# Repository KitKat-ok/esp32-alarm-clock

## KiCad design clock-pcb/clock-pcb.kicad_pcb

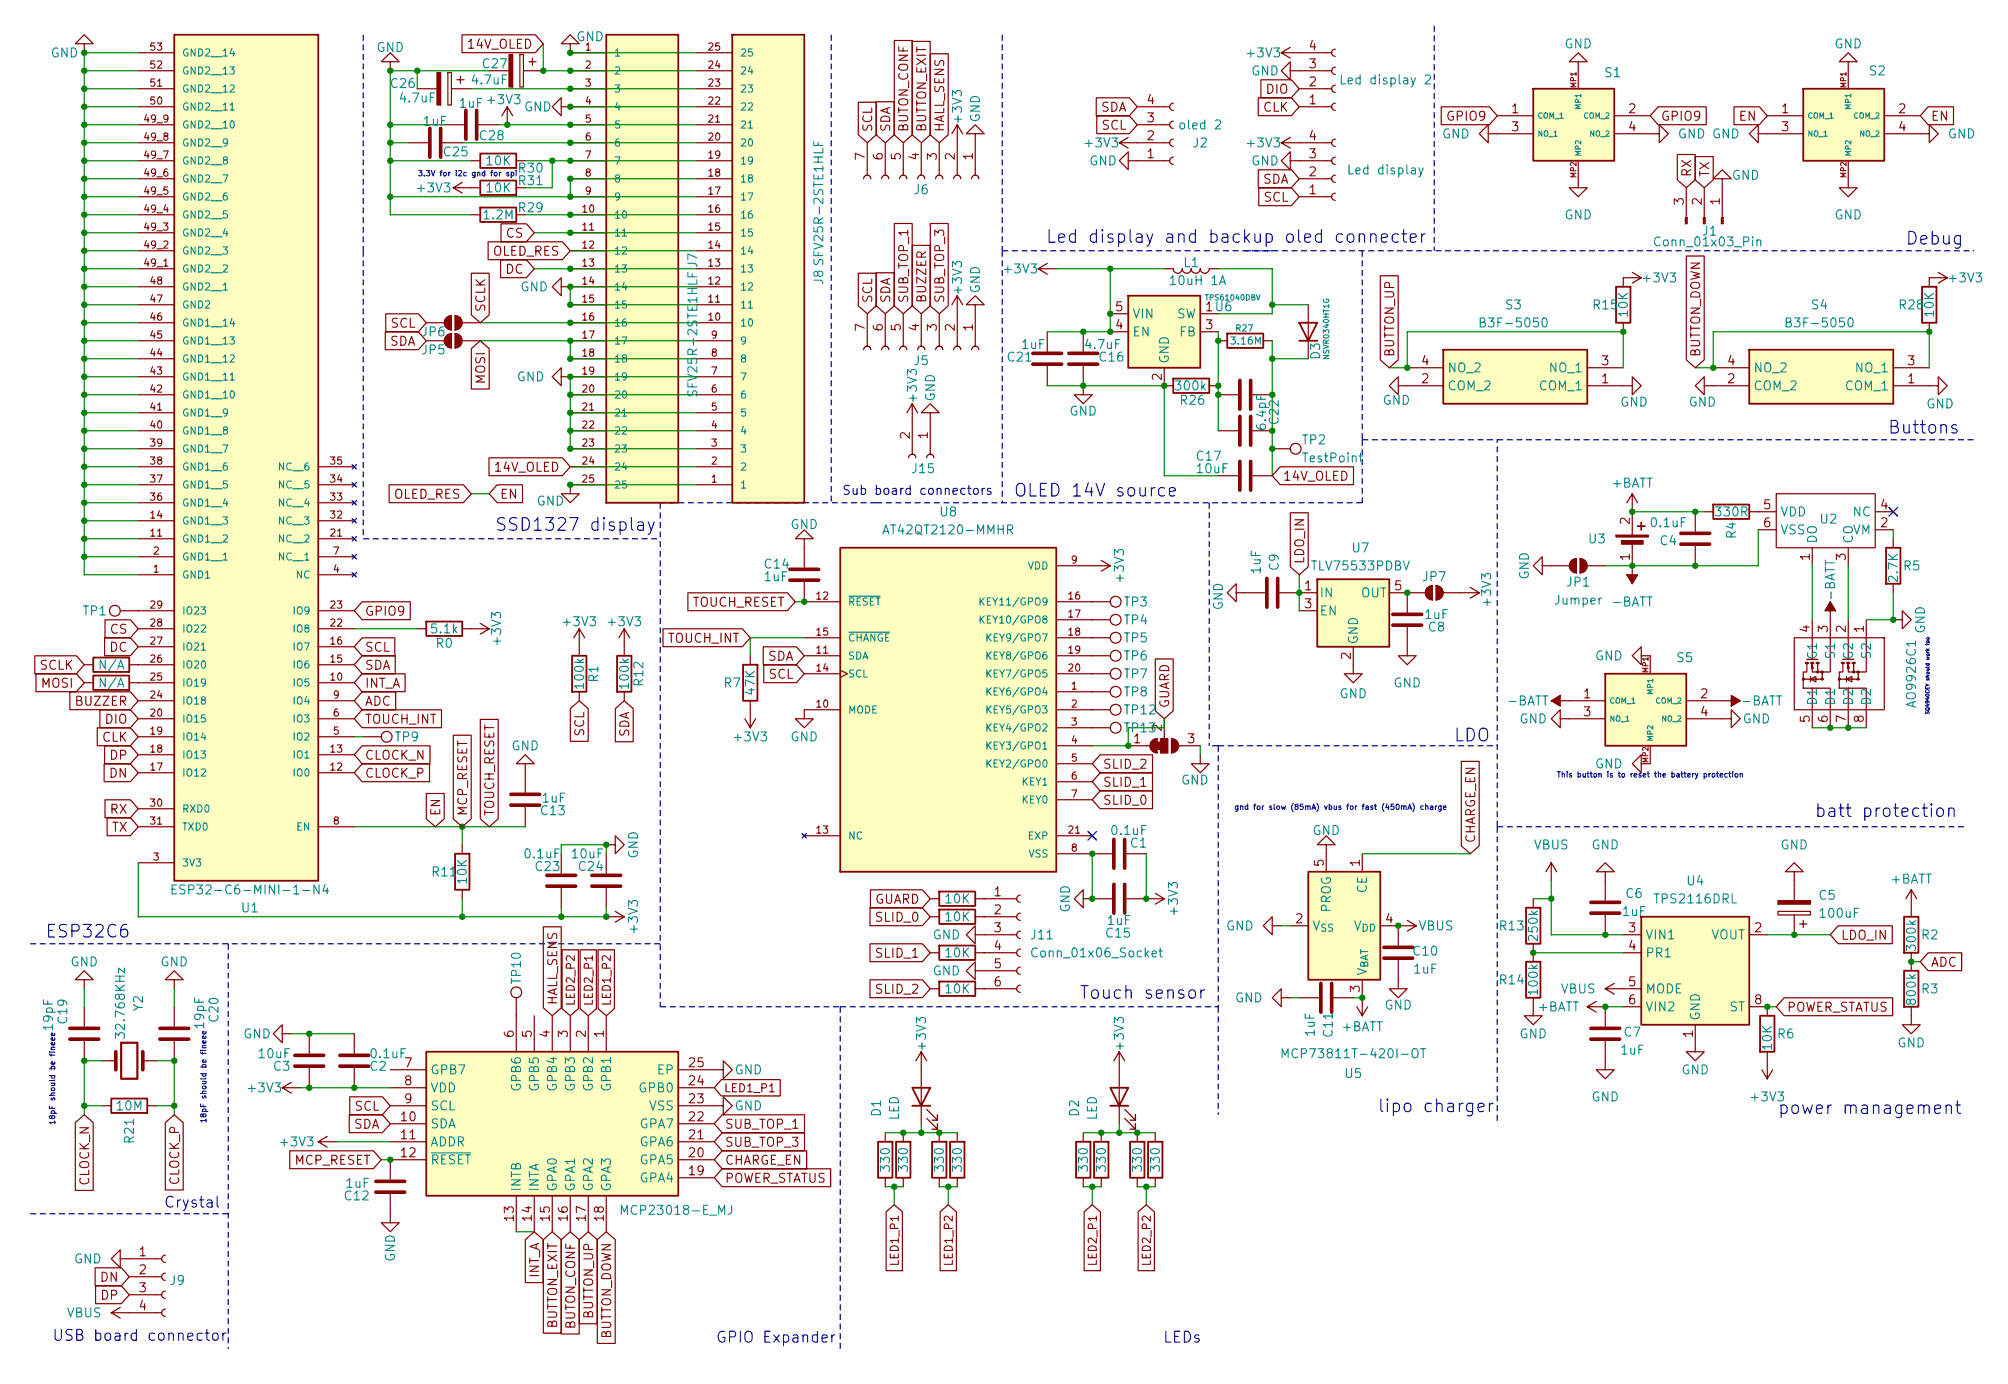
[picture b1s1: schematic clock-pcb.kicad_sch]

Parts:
AO9926C1: SOIC-8_3.9x4.9mm_P1.27mm
C1, C2, C4, C23: 0.1uF; C_0603_1608Metric
C3, C17, C24: 10uF; C_0603_1608Metric
C5: 100uF; CP_Radial_D5.0mm_P2.50mm
C6, C7, C8, C9, C10, C11, C12, C13, C14, C15, C21, C25, C28: 1uF; C_0603_1608Metric
C16: 4.7uF; C_0805_2012Metric
C18: 6.4pF; C_0402_1005Metric
C19, C20: 19pF; C_0402_1005Metric
C22: 6.4pF; C_01005_0402Metric
C26, C27: 4.7uF; CP_EIA-3528-12_Kemet-T
D1, D2: LED; LED_1210_3225Metric
D3: NSVR0340HT1G; D_SOD-323
IC2: MCP23018-E_MJ; QFN50P400X400X90-25N-D; Manufacturer_Part_Number MCP23018-E/MJ
J1: Conn_01x03_Pin; PinHeader_1x03_P2.54mm_Vertical
J2: oled 2; SSD1306_0.96_Oled
J3: Led display; tm1637_module
J4: Led display 2; PinHeader_1x04_P2.54mm_Vertical
J5, J6: Conn_01x07_Socket; PinHeader_1x07_P2.54mm_Vertical
J7: SFV25R-2STE1HLF; OLED_1.5IN_128X128MONO; PARTREV C
J8: SFV25R-2STE1HLF; AMPHENOL_SFV25R-2STE1HLF; PARTREV C
J9: Conn_01x04_Socket; JST_XH_B4B-XH-AM_1x04_P2.50mm_Vertical
J11: Conn_01x06_Socket; PinHeader_1x06_P2.54mm_Vertical
J15: Conn_01x02_Socket; PinSocket_1x02_P2.54mm_Vertical
JP1, JP5, JP6, JP7: Jumper; jumper_solder_small
JP2: SolderJumper_3_Bridged12; jumper_solder_small_3_bridged
L1: 10uH 1A; HPI0530-100
R0: 5.1k; R_0402_1005Metric
R1, R12, R14: 100k; R_0402_1005Metric
R2, R26: 300k; R_0402_1005Metric
R3: 800k; R_0402_1005Metric
R4: 330R; R_0402_1005Metric
R5: 2.7K; R_0402_1005Metric
R6, R8, R9, R10, R11, R15, R16, R28, R30, R31: 10K; R_0402_1005Metric
R7: 47K; R_0402_1005Metric
R13: 250k; R_0402_1005Metric
R17, R18, R19, R20, R22, R23, R24, R25: 330; R_0402_1005Metric
R21: 10M; R_0402_1005Metric
R27: 3.16M; R_0402_1005Metric
R29: 1.2M; R_0402_1005Metric
R32, R33: N/A; R_0402_1005Metric
S1, S2, S5: TS21-34-035-BK-160-SMT-TR; TS2134035BK160SMTTR; Mouser Part Number 179-134035BK160SMTTR
S3, S4: B3F-5050; B3F-4055; Manufacturer_Part_Number B3F-5050
TP1, TP3, TP4, TP5, TP6, TP7, TP8, TP9, TP10, TP12, TP13: TestPoint; TestPoint_THTPad_1.0x1.0mm_Drill0.5mm
TP2: TestPoint; TestPoint_Pad_D1.0mm
U1: ESP32-C6-MINI-1-N4; XCVR_ESP32-C6-MINI-1-N4; PARTREV 1.0
U2: SOT95P280X140-6N
U3: JST_XH_B2B-XH-AM_1x02_P2.50mm_Vertical
U4: TPS2116DRL; SOT-583-8
U5: MCP73811T-420I-OT; SOT-23-5
U6: TPS61040DBV; SOT-23-5
U7: TLV75533PDBV; TLV75733PDYDR
U8: AT42QT2120-MMHR; QFN45P300X300X85-21N; PARTREV E
Y2: 32.768KHz; XTAL_9HT10_TXC

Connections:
14V_OLED: C17.1, C18.1, C22.1, C27.1, D3.1 (K), J7.2, J7.24, J8.2, J8.24, R27.1, TP2.1
+3V3: C1.2, C2.1, C3.1, C15.2, C16.1, C21.2, C23.1, C24.1, C28.2, D1.2 (A), D2.2 (A), IC2.8 (VDD), IC2.11 (ADDR), J2.2, J3.4, J4.4, J5.2, J6.2, J7.5, J8.21, J15.2, JP7.2 (B), L1.2, R0.1, R1.1, R6.2, R7.1, R11.1, R12.1, R15.2, R28.2, R31.1, U1.3 (3V3), U6.4 (EN), U6.5 (VIN), U8.9 (VDD)
+BATT: C4.2, C7.1, C11.1, R2.1, R4.2, U3.2, U4.6 (VIN2), U5.3 (V_{BAT})
-BATT: AO9926C1.3 (S1), C4.1, JP1.1 (A), S5.1 (COM_1), S5.2 (COM_2), U2.6 (VSS), U3.1
ADC: R2.2, R3.1, U1.9 (IO4)
BUTON_CONF: IC2.16 (GPA1), J6.5
BUTTON_DOWN: IC2.18 (GPA3), R28.1, S4.3 (NO_1), S4.4 (NO_2)
BUTTON_EXIT: IC2.15 (GPA0), J6.4
BUTTON_UP: IC2.17 (GPA2), R15.1, S3.3 (NO_1), S3.4 (NO_2)
BUZZER: J5.4, U1.24 (IO18)
CHARGE_EN: IC2.20 (GPA5), U5.1 (CE)
CLK: J4.1, U1.19 (IO14)
CLOCK_N: C19.1, R21.1, U1.13 (IO1), Y2.1
CLOCK_P: C20.1, R21.2, U1.12 (IO0), Y2.2
CS: J7.11, J8.15, U1.28 (IO22)
DC: J7.13, J8.13, U1.27 (IO21)
DIO: J4.2, U1.20 (IO15)
DN: J9.2, U1.17 (IO12)
DP: J9.3, U1.18 (IO13)
EN: C12.2, C13.1, C14.2, IC2.12 (~RESET), J7.12, J8.14, R11.2, S2.1 (COM_1), S2.2 (COM_2), U1.8 (EN), U8.12 (~RESET)
GND: AO9926C1.1 (S2), C1.1, C2.2, C3.2, C5.2, C6.1, C7.2, C8.2, C9.2, C10.2, C11.2, C12.1, C13.2, C14.1, C15.1, C16.2, C17.2, C19.2, C20.2, C21.1, C23.2, C24.2, C25.1, C26.2, C27.2, C28.1, IC2.23 (VSS), IC2.25 (EP), J1.1, J2.1, J3.3, J4.3, J5.1, J6.1, J7.1, J7.4, J7.8, J7.9, J7.14, J7.15, J7.19, J7.20, J7.21, J7.22, J7.23, J7.25, J8.1, J8.3, J8.4, J8.5, J8.6, J8.7, J8.11, J8.12, J8.17, J8.18, J8.22, J8.25, J9.1, J11.3, J11.5, J15.1, JP1.2 (B), JP2.3 (B), R3.2, R5.2, R14.1, R26.2, R29.2, R30.1, S1.3 (NO_1), S1.4 (NO_2), S1.MP1, S1.MP2, S2.3 (NO_1), S2.4 (NO_2), S2.MP1, S2.MP2, S3.1 (COM_1), S3.2 (COM_2), S4.1 (COM_1), S4.2 (COM_2), S5.3 (NO_1), S5.4 (NO_2), S5.MP1, S5.MP2, U1.1 (GND1), U1.2 (GND1__1), U1.11 (GND1__2), U1.14 (GND1__3), U1.36 (GND1__4), U1.37 (GND1__5), U1.38 (GND1__6), U1.39 (GND1__7), U1.40 (GND1__8), U1.41 (GND1__9), U1.42 (GND1__10), U1.43 (GND1__11), U1.44 (GND1__12), U1.45 (GND1__13), U1.46 (GND1__14), U1.47 (GND2), U1.48 (GND2__1), U1.49_1 (GND2__2), U1.49_2 (GND2__3), U1.49_3 (GND2__4), U1.49_4 (GND2__5), U1.49_5 (GND2__6), U1.49_6 (GND2__7), U1.49_7 (GND2__8), U1.49_8 (GND2__9), U1.49_9 (GND2__10), U1.50 (GND2__11), U1.51 (GND2__12), U1.52 (GND2__13), U1.53 (GND2__14), U4.1 (GND), U5.2 (V_{SS}), U5.5 (PROG), U6.2 (GND), U7.2 (GND), U8.8 (VSS), U8.10 (MODE)
GPIO9: S1.1 (COM_1), S1.2 (COM_2), U1.23 (IO9)
GUARD: JP2.1 (A), JP2.2 (C), R9.2, U8.4 (KEY3/GPO1)
HALL_SENS: IC2.4 (GPB4), J6.3
INT_A: IC2.13 (INTB), IC2.14 (INTA), U1.10 (IO5)
LDO_IN: C5.1, C9.1, U4.2 (VOUT), U4.7 (VOUT), U7.1 (IN), U7.3 (EN)
LED1_P1: IC2.24 (GPB0), R17.1, R19.1
LED1_P2: IC2.1 (GPB1), R18.1, R20.1
LED2_P1: IC2.2 (GPB2), R22.1, R23.1
LED2_P2: IC2.3 (GPB3), R24.1, R25.1
MOSI: J7.17, J7.18, J8.8, J8.9, JP5.2 (B), R33.1
unnamed: AO9926C1.5 (D1), AO9926C1.6 (D1), AO9926C1.7 (D2), AO9926C1.8 (D2)
unnamed: AO9926C1.4 (G1), U2.1 (DO)
unnamed: AO9926C1.2 (G2), U2.3 (CO)
unnamed: C25.2, J7.6, J8.20
unnamed: C26.1, J7.3, J8.23
unnamed: D1.1 (K), R17.2, R18.2, R19.2, R20.2
unnamed: D2.1 (K), R22.2, R23.2, R24.2, R25.2
unnamed: D3.2 (A), L1.1, U6.1 (SW)
unnamed: IC2.6 (GPB6), TP10.1
unnamed: J7.7, J8.19, R30.2, R31.2
unnamed: J7.10, J8.16, R29.1
unnamed: J11.1, R9.1
unnamed: J11.2, R16.1
unnamed: J11.4, R10.1
unnamed: J11.6, R8.1
unnamed: C8.1, JP7.1 (A), U7.5 (OUT)
unnamed: TP9.1, U1.5 (IO2)
unnamed: R0.2, U1.22 (IO8)
unnamed: R33.2, U1.25 (IO19)
unnamed: R32.2, U1.26 (IO20)
unnamed: TP1.1, U1.29 (IO23)
unnamed: R4.1, U2.5 (VDD)
unnamed: R5.1, U2.2 (VM)
unnamed: R13.1, R14.2, U4.4 (PR1)
unnamed: C18.2, C22.2, R26.1, R27.2, U6.3 (FB)
unnamed: TP13.1, U8.3 (KEY4/GPO2)
unnamed: TP12.1, U8.2 (KEY5/GPO3)
unnamed: TP8.1, U8.1 (KEY6/GPO4)
unnamed: TP7.1, U8.20 (KEY7/GPO5)
unnamed: TP6.1, U8.19 (KEY8/GPO6)
unnamed: TP5.1, U8.18 (KEY9/GPO7)
unnamed: TP4.1, U8.17 (KEY10/GPO8)
unnamed: TP3.1, U8.16 (KEY11/GPO9)
POWER_STATUS: IC2.19 (GPA4), R6.1, U4.8 (ST)
RX: J1.3, U1.30 (RXD0)
SCL: IC2.9 (SCL), J2.3, J3.1, J5.7, J6.7, JP6.1 (A), R1.2, U1.16 (IO7), U8.14 (SCL)
SCLK: J7.16, J8.10, JP6.2 (B), R32.1
SDA: IC2.10 (SDA), J2.4, J3.2, J5.6, J6.6, JP5.1 (A), R12.2, U1.15 (IO6), U8.11 (SDA)
SLID_0: R16.2, U8.7 (KEY0)
SLID_1: R10.2, U8.6 (KEY1)
SLID_2: R8.2, U8.5 (KEY2/GPO0)
SUB_TOP_1: IC2.22 (GPA7), J5.5
SUB_TOP_3: IC2.21 (GPA6), J5.3
TOUCH_INT: R7.2, U1.6 (IO3), U8.15 (~CHANGE)
TX: J1.2, U1.31 (TXD0)
VBUS: C6.2, C10.1, J9.4, R13.2, U4.3 (VIN1), U4.5 (MODE), U5.4 (V_{DD})

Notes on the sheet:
batt protection
Debug
power management
OLED 14V source
lipo charger
18pF should be fineee
SQ4940CEY should work too
Buttons
Led display and backup oled connecter
Sub board connectors
This button is to reset the battery protection
Touch sensor
gnd for slow (85mA) vbus for fast (450mA) charge
GPIO Expander
ESP32C6
Crystal
USB board connector
LDO
3.3V for i2c gnd for spi
SSD1327 display
LEDs

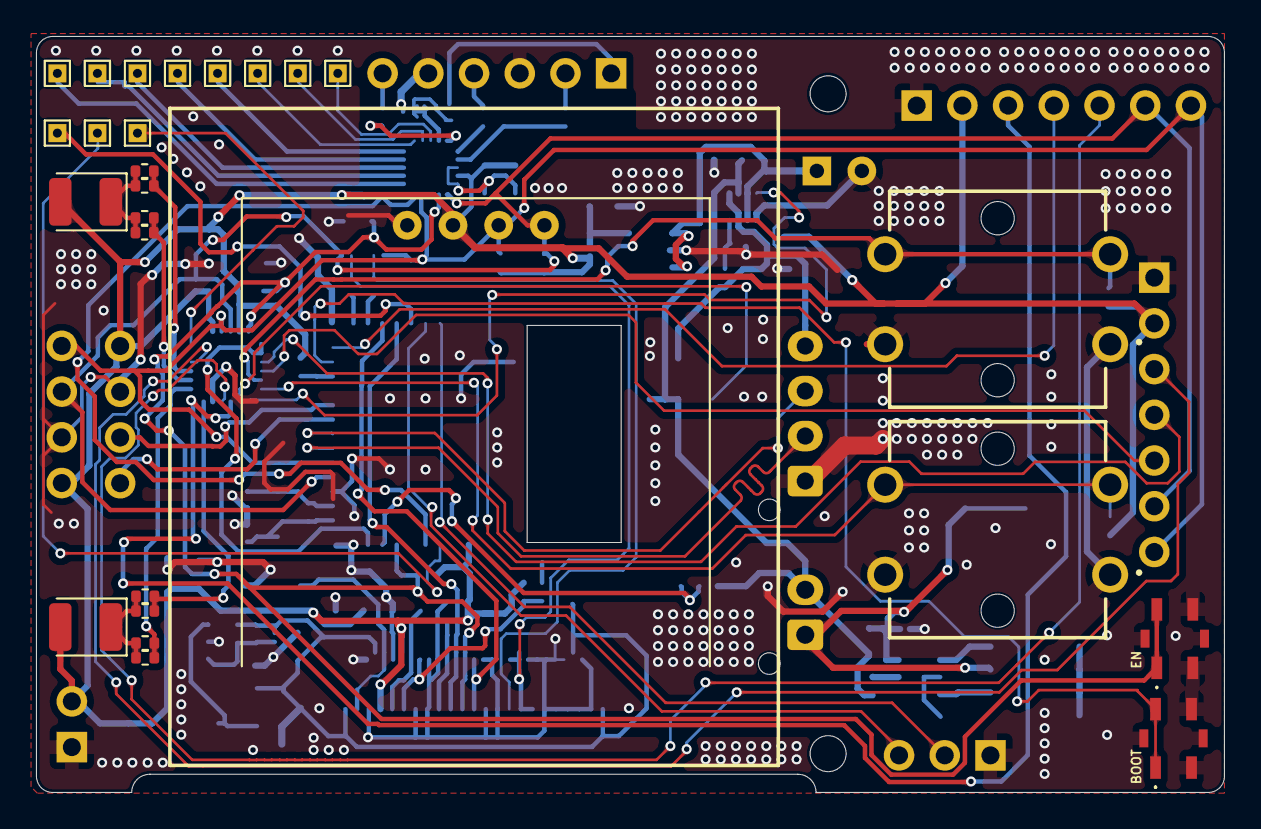
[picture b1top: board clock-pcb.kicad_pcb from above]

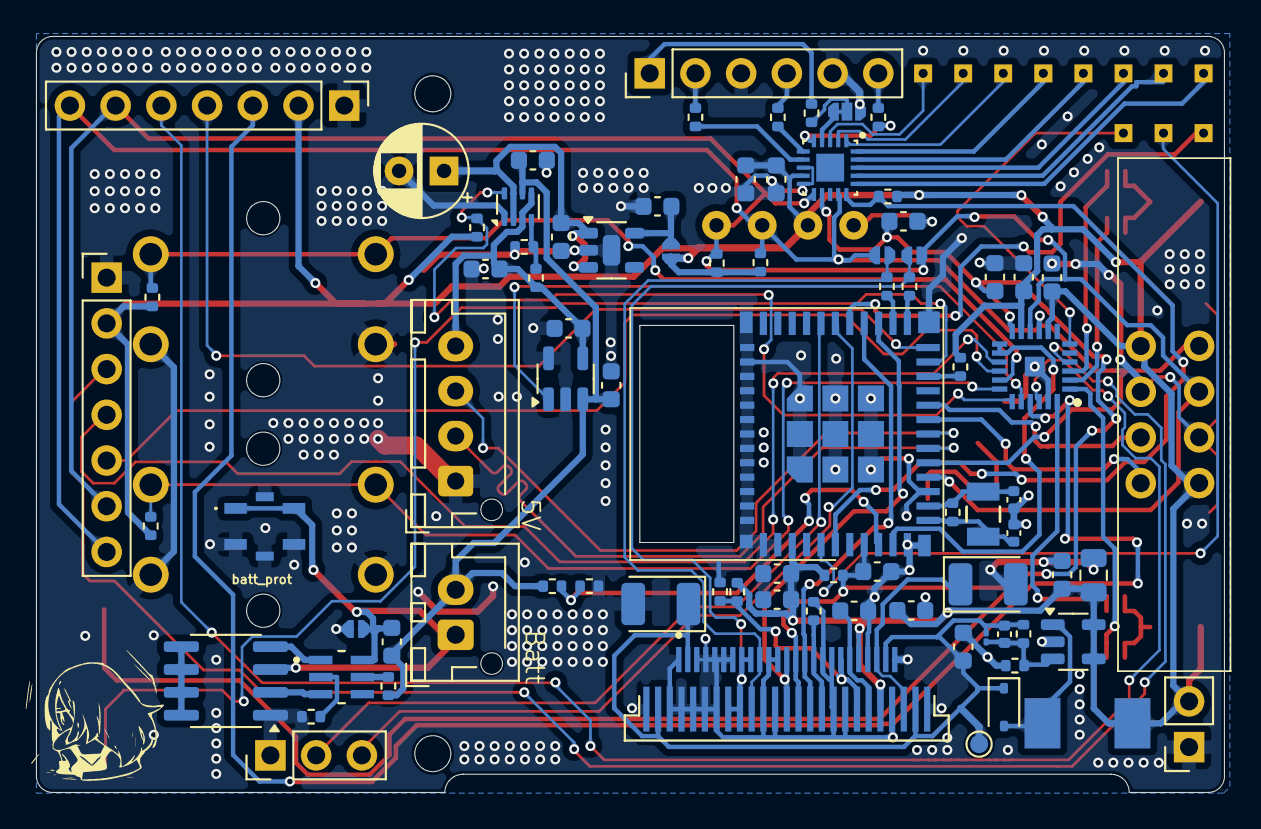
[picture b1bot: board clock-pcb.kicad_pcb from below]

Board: 2 copper layers, 66.0 x 42.0 mm, 110 parts (81 on the bottom side), 77 nets.

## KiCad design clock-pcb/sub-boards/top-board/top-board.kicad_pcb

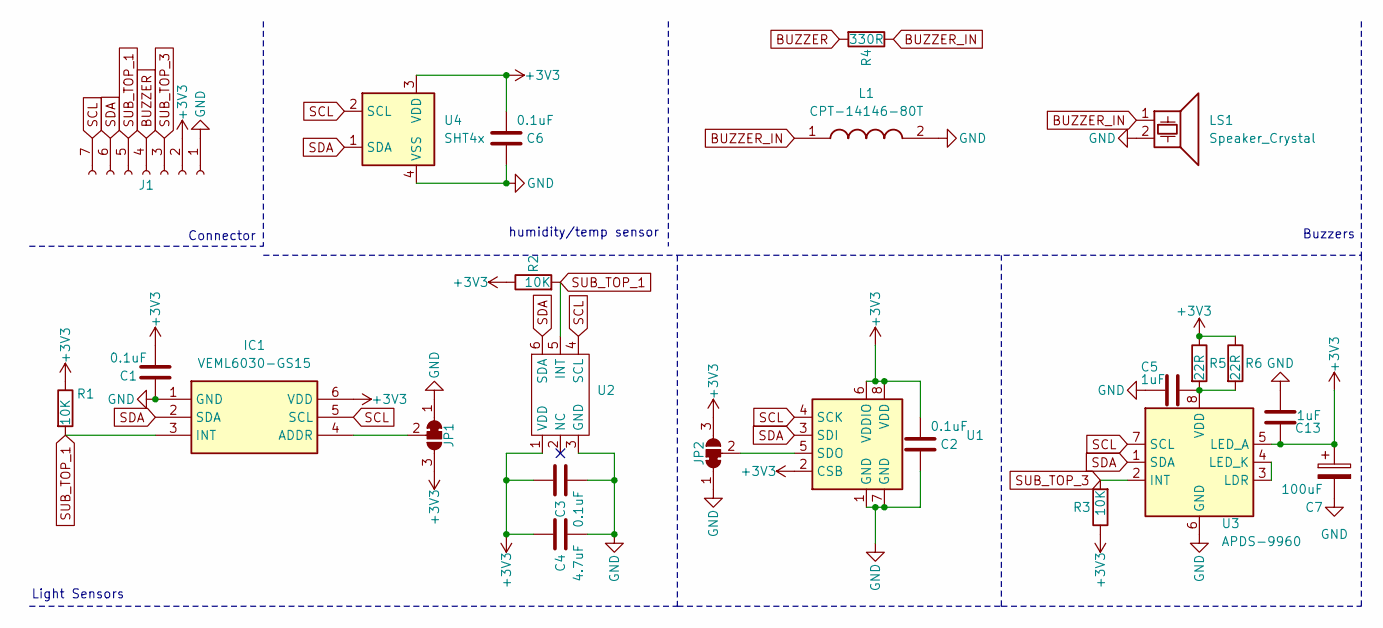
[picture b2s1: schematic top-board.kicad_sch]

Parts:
C1, C2, C3, C6: 0.1uF; C_0603_1608Metric
C4: 4.7uF; C_0603_1608Metric
C5, C13: 1uF; C_0603_1608Metric
C7: 100uF; CP_Radial_D5.0mm_P2.50mm
IC1: VEML6030-GS15; VEML6030GS15; Mouser Part Number 78-VEML6030-GS15
J1: Conn_01x07_Socket; PinHeader_1x07_P2.54mm_Horizontal
JP1, JP2: SolderJumper_3_Bridged12; SolderJumper-3_P1.3mm_Bridged2Bar12_RoundedPad1.0x1.5mm
L1: CPT-14146-80T; CPT1414680T; Mouser Part Number 490-CPT-14146-80T
LS1: Speaker_Crystal; AST0760_MAL
R1, R2, R3: 10K; R_0402_1005Metric
R4: 330R; R_0402_1005Metric
R5: 22R; R_0402_1005Metric
R6: 22R; R_Axial_DIN0204_L3.6mm_D1.6mm_P2.54mm_Vertical
U1: BMP280; Bosch_LGA-8_2x2.5mm_P0.65mm_ClockwisePinNumbering
U2: LTR-F216A
U3: APDS-9960; Avago_APDS-9960
U4: SHT4x; Sensirion_DFN-4_1.5x1.5mm_P0.8mm_SHT4x_NoCentralPad

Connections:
+3V3: C1.2, C2.2, C3.1, C4.1, C6.2, C7.1, C13.1, IC1.6 (VDD), J1.2, JP1.3 (B), JP2.3 (B), R1.1, R2.1, R3.1, R5.1, R6.1, U1.2 (CSB), U1.6 (VDDIO), U1.8 (VDD), U2.1 (VDD), U3.5 (LED_A), U4.3 (VDD)
BUZZER: J1.4, R4.2
BUZZER_IN: L1.1, LS1.1, R4.1
GND: C1.1, C2.1, C3.2, C4.2, C5.2, C6.1, C7.2, C13.2, IC1.1 (GND), J1.1, JP1.1 (A), JP2.1 (A), L1.2, LS1.2, U1.1 (GND), U1.7 (GND), U2.3 (GND), U3.6 (GND), U4.4 (VSS)
unnamed: IC1.4 (ADDR), JP1.2 (C)
unnamed: JP2.2 (C), U1.5 (SDO)
unnamed: U3.3 (LDR), U3.4 (LED_K)
unnamed: C5.1, R5.2, R6.2, U3.8 (VDD)
SCL: IC1.5 (SCL), J1.7, U1.4 (SCK), U2.4 (SCL), U3.7 (SCL), U4.2 (SCL)
SDA: IC1.2 (SDA), J1.6, U1.3 (SDI), U2.6 (SDA), U3.1 (SDA), U4.1 (SDA)
SUB_TOP_1: IC1.3 (INT), J1.5, R1.2, R2.2, U2.5 (INT)
SUB_TOP_3: J1.3, R3.2, U3.2 (INT)

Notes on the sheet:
Buzzers
Light Sensors
humidity/temp sensor
Connector

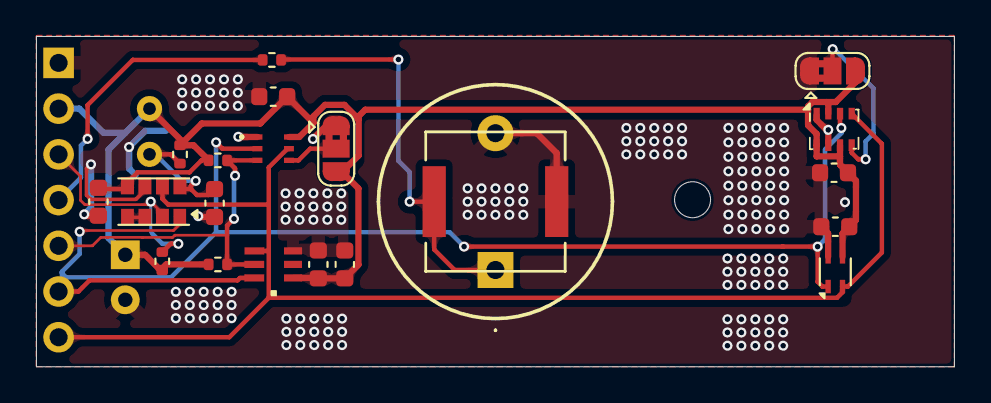
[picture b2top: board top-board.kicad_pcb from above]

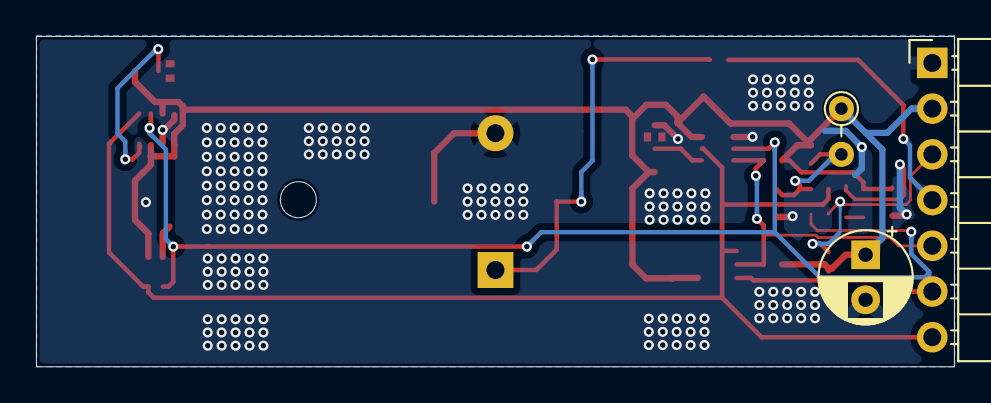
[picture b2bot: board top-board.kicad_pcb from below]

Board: 2 copper layers, 51.0 x 18.3 mm, 24 parts (3 on the bottom side), 12 nets.

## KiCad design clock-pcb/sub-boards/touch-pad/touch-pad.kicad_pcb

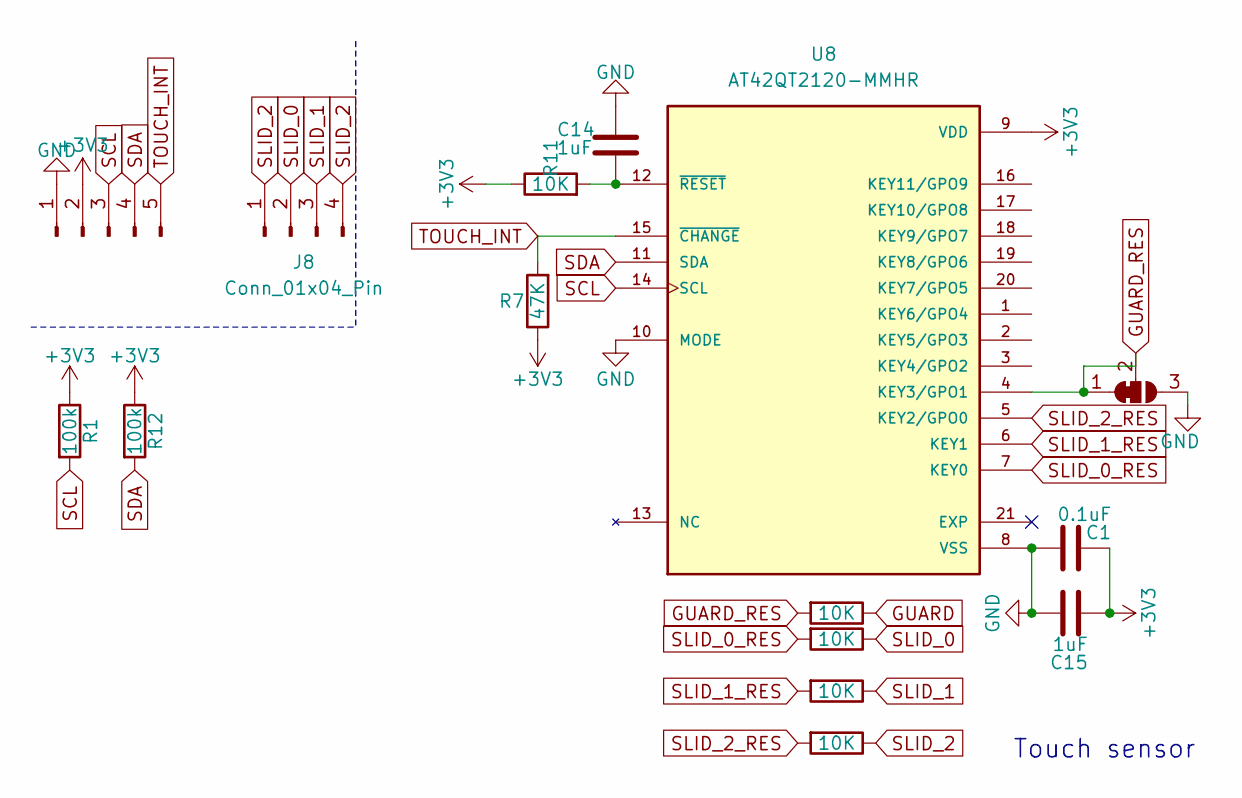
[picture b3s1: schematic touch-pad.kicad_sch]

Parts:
C1: 0.1uF; C_0603_1608Metric
C14, C15: 1uF; C_0603_1608Metric
J7: Conn_01x05_Pin; PinHeader_1x05_P2.54mm_Vertical
J8: Conn_01x04_Pin; TouchSlider-4_90x55mm
JP2: SolderJumper_3_Bridged12; jumper_solder_small_3_bridged
R1, R12: 100k; R_0402_1005Metric
R7: 47K; R_0402_1005Metric
R8, R9, R10, R11, R16: 10K; R_0402_1005Metric
U8: AT42QT2120-MMHR; QFN45P300X300X85-21N; PARTREV E

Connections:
+3V3: C1.2, C15.2, J7.2, R1.1, R7.1, R11.1, R12.1, U8.9 (VDD)
GND: C1.1, C14.1, C15.1, J7.1, JP2.3 (B), U8.8 (VSS), U8.10 (MODE)
GUARD: R9.1
GUARD_RES: JP2.1 (A), JP2.2 (C), R9.2, U8.4 (KEY3/GPO1)
unnamed: C14.2, R11.2, U8.12 (~RESET)
SCL: J7.3, R1.2, U8.14 (SCL)
SDA: J7.4, R12.2, U8.11 (SDA)
SLID_0: J8.2, R16.1
SLID_0_RES: R16.2, U8.7 (KEY0)
SLID_1: J8.3, R10.1
SLID_1_RES: R10.2, U8.6 (KEY1)
SLID_2: J8.1, J8.4, R8.1
SLID_2_RES: R8.2, U8.5 (KEY2/GPO0)
TOUCH_INT: J7.5, R7.2, U8.15 (~CHANGE)

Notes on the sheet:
Touch sensor

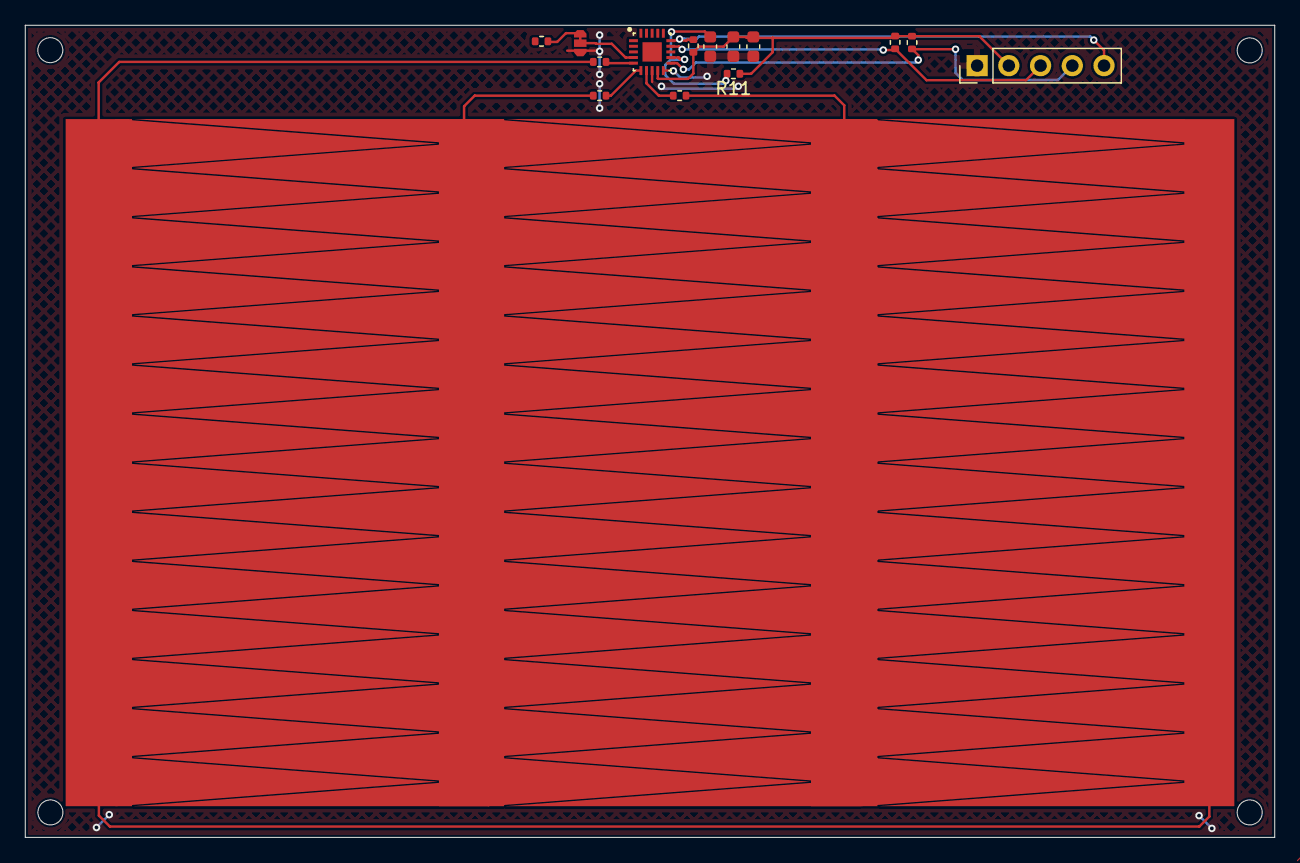
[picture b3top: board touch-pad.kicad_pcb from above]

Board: 2 copper layers, 100.0 x 65.0 mm, 15 parts (0 on the bottom side), 13 nets.

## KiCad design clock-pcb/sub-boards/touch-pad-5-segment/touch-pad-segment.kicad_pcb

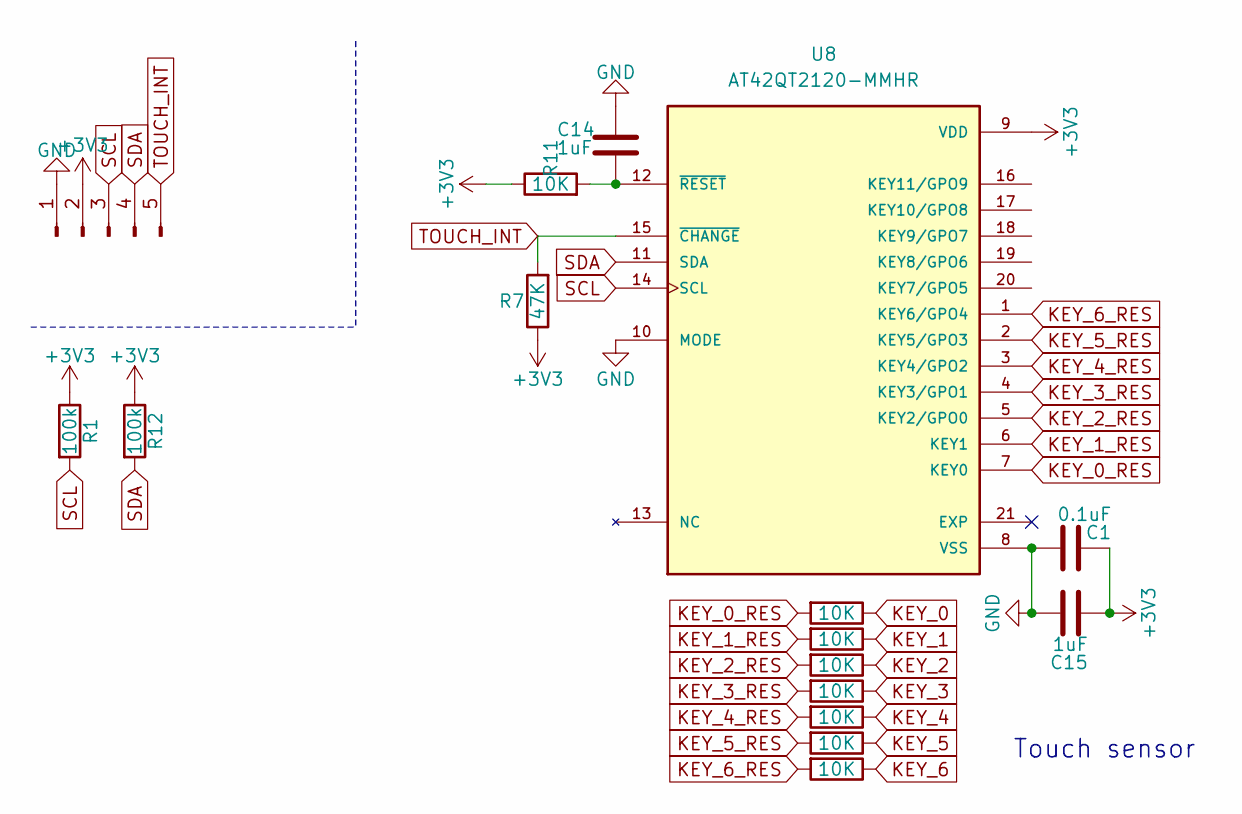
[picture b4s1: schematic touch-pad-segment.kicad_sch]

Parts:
C1: 0.1uF; C_0603_1608Metric
C14, C15: 1uF; C_0603_1608Metric
J7: Conn_01x05_Pin; PinHeader_1x05_P2.54mm_Vertical
R1, R12: 100k; R_0402_1005Metric
R2, R3, R4, R8, R9, R10, R11, R16: 10K; R_0402_1005Metric
R7: 47K; R_0402_1005Metric
U8: AT42QT2120-MMHR; QFN45P300X300X85-21N; PARTREV E

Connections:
+3V3: C1.2, C15.2, J7.2, R1.1, R7.1, R11.1, R12.1, U8.9 (VDD)
GND: C1.1, C14.1, C15.1, J7.1, U8.8 (VSS), U8.10 (MODE)
KEY_0: R9.1
KEY_0_RES: R9.2, U8.7 (KEY0)
KEY_1: R16.1
KEY_1_RES: R16.2, U8.6 (KEY1)
KEY_2: R2.1
KEY_2_RES: R2.2, U8.5 (KEY2/GPO0)
KEY_3: R10.1
KEY_3_RES: R10.2, U8.4 (KEY3/GPO1)
KEY_4: R8.1
KEY_4_RES: R8.2, U8.3 (KEY4/GPO2)
KEY_5: R3.1
KEY_5_RES: R3.2, U8.2 (KEY5/GPO3)
KEY_6: R4.1
KEY_6_RES: R4.2, U8.1 (KEY6/GPO4)
unnamed: C14.2, R11.2, U8.12 (~RESET)
SCL: J7.3, R1.2, U8.14 (SCL)
SDA: J7.4, R12.2, U8.11 (SDA)
TOUCH_INT: J7.5, R7.2, U8.15 (~CHANGE)

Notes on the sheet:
Touch sensor

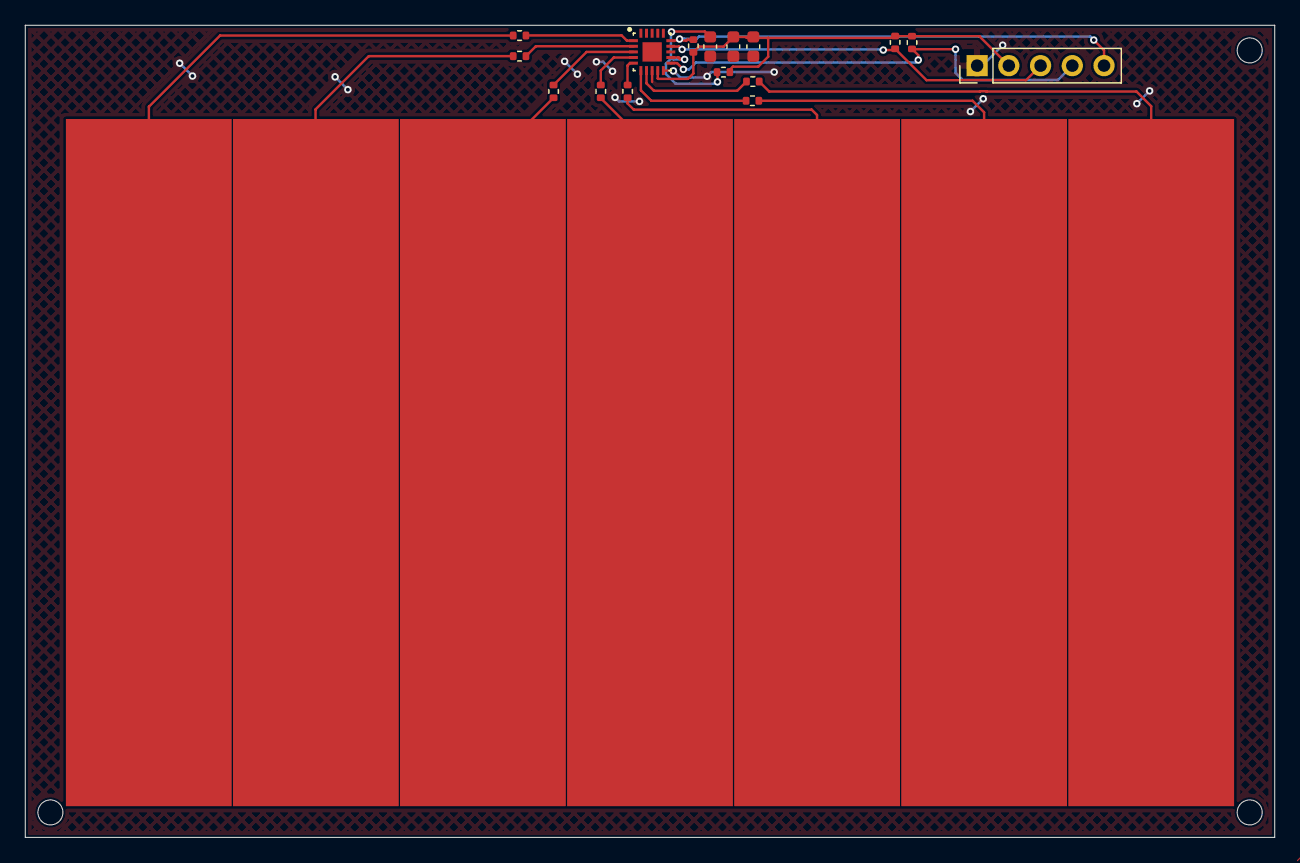
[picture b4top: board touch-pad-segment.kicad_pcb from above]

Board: 2 copper layers, 100.0 x 65.0 mm, 16 parts (0 on the bottom side), 13 nets.

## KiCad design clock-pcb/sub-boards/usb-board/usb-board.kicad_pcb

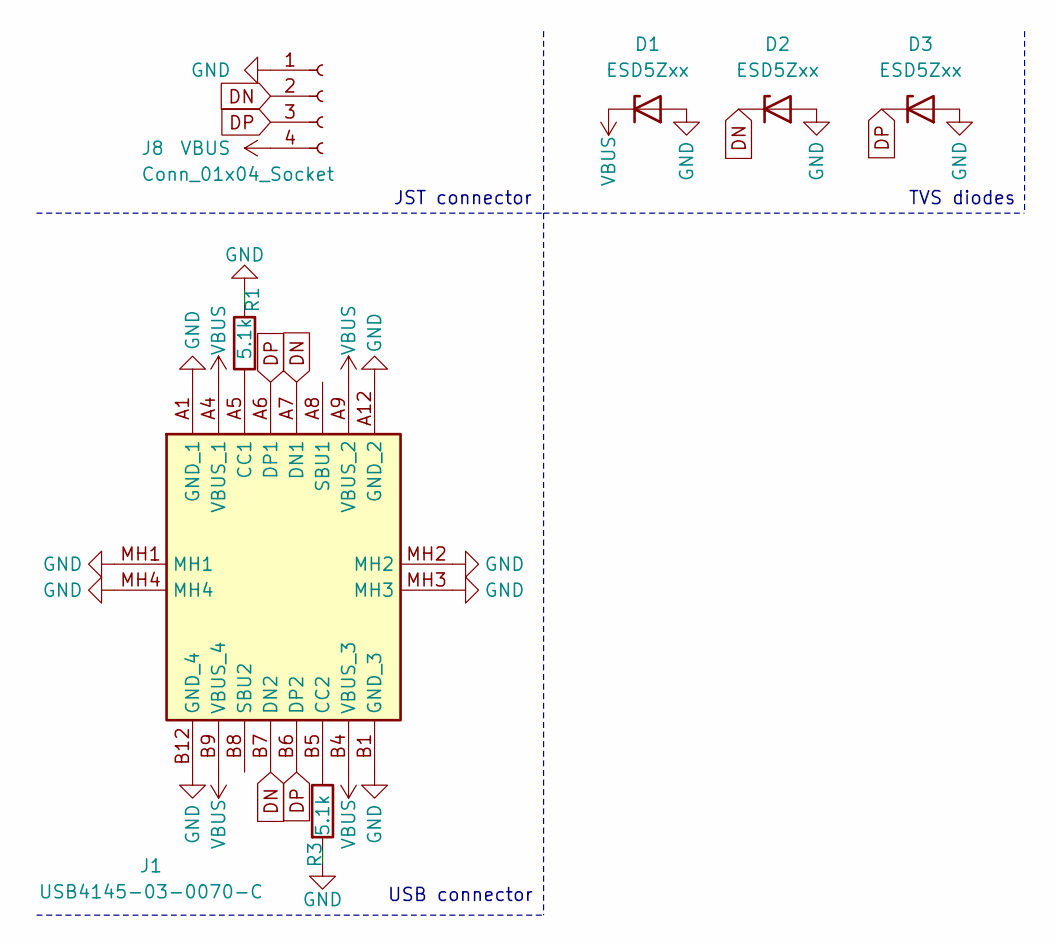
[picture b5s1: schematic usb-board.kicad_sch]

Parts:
D1, D2, D3: ESD5Zxx; D_SOD-523
J1: USB4145-03-0070-C; USB4145030070C; Mouser Part Number 640-USB4145-3-0070-C
J8: Conn_01x04_Socket; JST_XH_B4B-XH-AM_1x04_P2.50mm_Vertical
R1, R3: 5.1k; R_0402_1005Metric

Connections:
DN: D2.1 (K), J1.A7 (DN1), J1.B7 (DN2), J8.2
DP: D3.1 (K), J1.A6 (DP1), J1.B6 (DP2), J8.3
GND: D1.2 (A), D2.2 (A), D3.2 (A), J1.A1 (GND_1), J1.A12 (GND_2), J1.B1 (GND_3), J1.B12 (GND_4), J1.MH1, J1.MH2, J1.MH3, J1.MH4, J8.1, R1.2, R3.2
unnamed: J1.A5 (CC1), R1.1
unnamed: J1.B5 (CC2), R3.1
VBUS: D1.1 (K), J1.A4 (VBUS_1), J1.A9 (VBUS_2), J1.B4 (VBUS_3), J1.B9 (VBUS_4), J8.4

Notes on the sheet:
TVS diodes
JST connector
USB connector

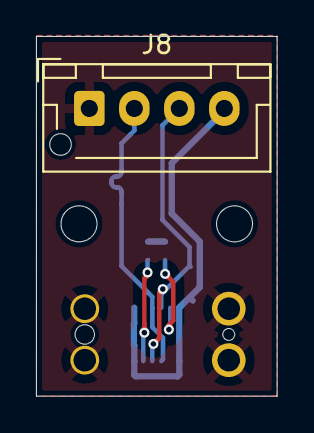
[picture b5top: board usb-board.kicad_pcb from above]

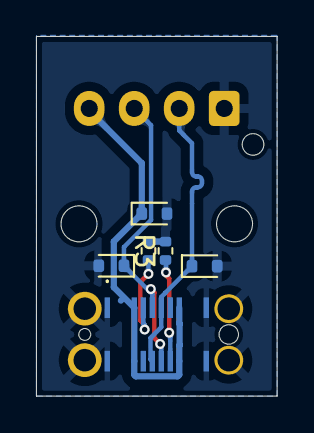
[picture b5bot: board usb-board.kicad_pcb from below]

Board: 2 copper layers, 13.4 x 20.0 mm, 7 parts (6 on the bottom side), 6 nets.

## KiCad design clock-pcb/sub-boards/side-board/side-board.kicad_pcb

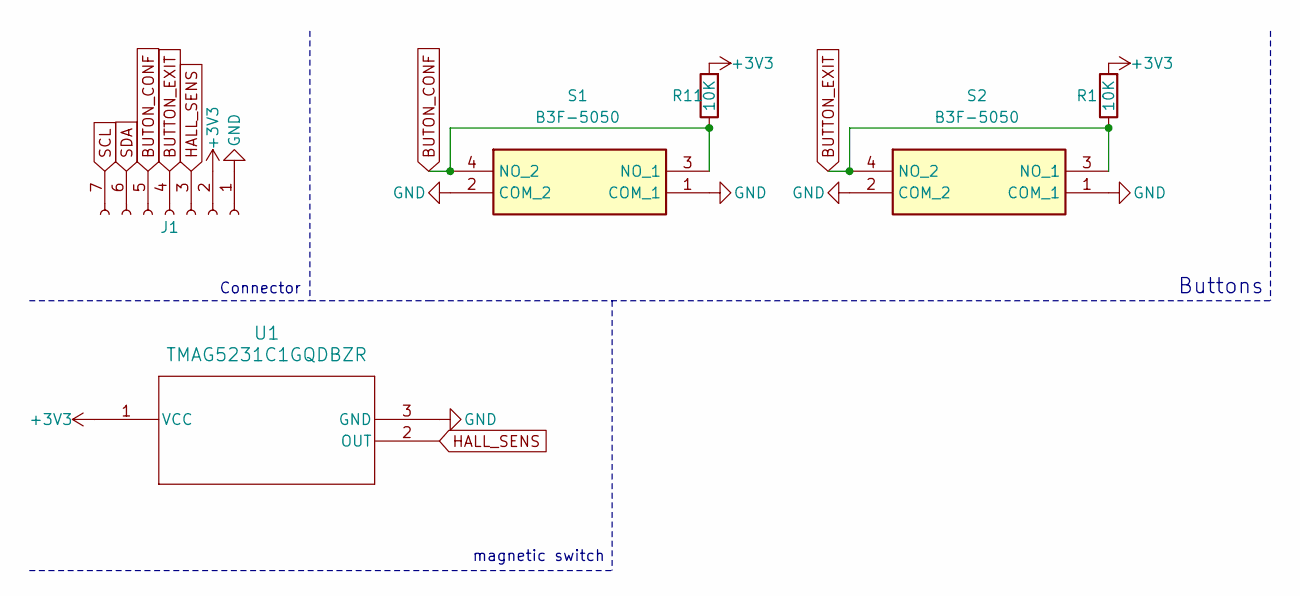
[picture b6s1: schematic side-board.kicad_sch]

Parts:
J1: Conn_01x07_Socket; PinHeader_1x07_P2.54mm_Horizontal
R1, R11: 10K; R_0402_1005Metric
S1, S2: B3F-5050; B3F-4055; Manufacturer_Part_Number B3F-5050
U1: TMAG5231C1GQDBZR; SOT-23-3

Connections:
+3V3: J1.2, R1.2, R11.2, U1.1 (VCC)
BUTON_CONF: J1.5, R11.1, S1.3 (NO_1), S1.4 (NO_2)
BUTTON_EXIT: J1.4, R1.1, S2.3 (NO_1), S2.4 (NO_2)
GND: J1.1, S1.1 (COM_1), S1.2 (COM_2), S2.1 (COM_1), S2.2 (COM_2), U1.3 (GND)
HALL_SENS: J1.3, U1.2 (OUT)
SCL: J1.7
SDA: J1.6

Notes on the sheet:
magnetic switch
Buttons
Connector

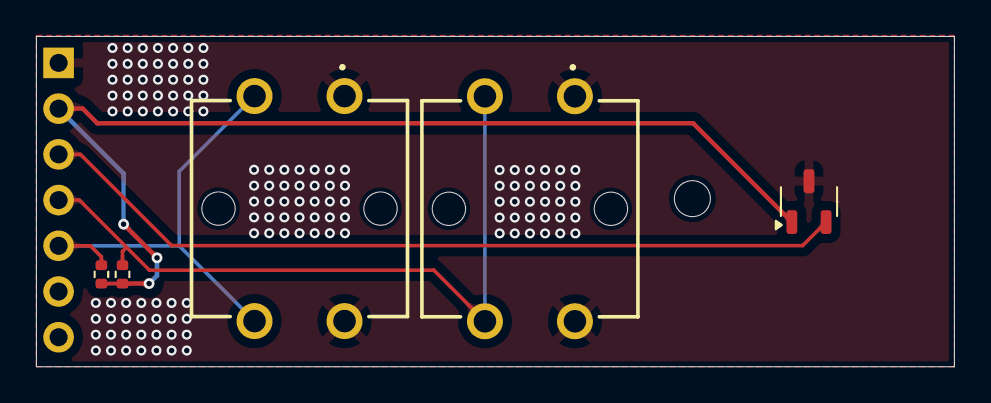
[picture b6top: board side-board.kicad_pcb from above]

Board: 2 copper layers, 51.0 x 18.3 mm, 6 parts (1 on the bottom side), 5 nets.

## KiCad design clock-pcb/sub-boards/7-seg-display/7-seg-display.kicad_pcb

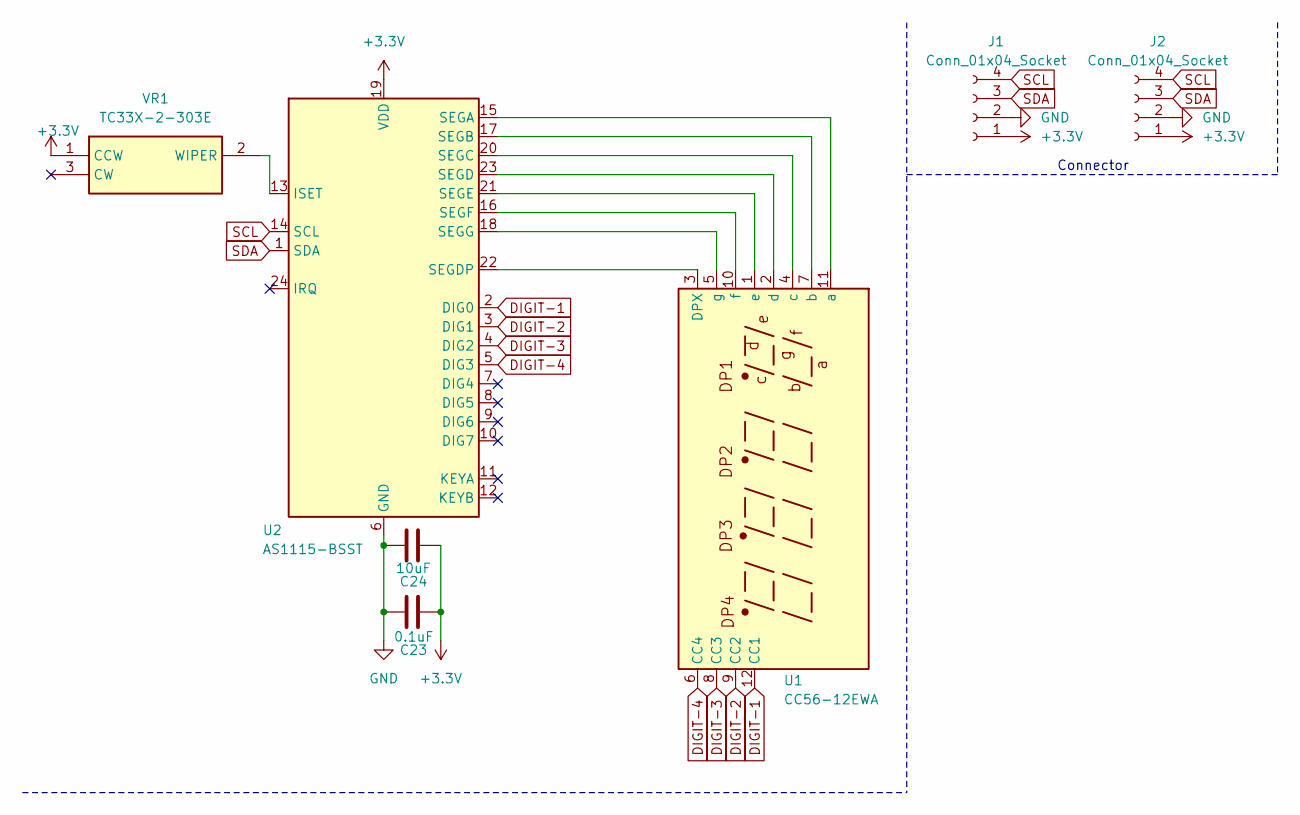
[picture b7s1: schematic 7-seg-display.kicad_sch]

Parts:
C23: 0.1uF; C_0603_1608Metric
C24: 10uF; C_0603_1608Metric
J1, J2: Conn_01x04_Socket; PinHeader_1x04_P2.54mm_Vertical
U1: CC56-12EWA; CA56-12EWA
U2: AS1115-BSST; QSOP-24_3.9x8.7mm_P0.635mm
VR1: TC33X-2-303E; TC33X2304E; Mouser Part Number 652-TC33X-2-303E

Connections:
+3.3V: C23.1, C24.1, J1.1, J2.1, U2.19 (VDD), VR1.1 (CCW)
DIGIT-1: U1.12 (CC1), U2.2 (DIG0)
DIGIT-2: U1.9 (CC2), U2.3 (DIG1)
DIGIT-3: U1.8 (CC3), U2.4 (DIG2)
DIGIT-4: U1.6 (CC4), U2.5 (DIG3)
GND: C23.2, C24.2, J1.2, J2.2, U2.6 (GND)
unnamed: U1.3 (DPX), U2.22 (SEGDP)
unnamed: U1.11 (a), U2.15 (SEGA)
unnamed: U1.7 (b), U2.17 (SEGB)
unnamed: U1.4 (c), U2.20 (SEGC)
unnamed: U1.2 (d), U2.23 (SEGD)
unnamed: U1.1 (e), U2.21 (SEGE)
unnamed: U1.10 (f), U2.16 (SEGF)
unnamed: U1.5 (g), U2.18 (SEGG)
unnamed: U2.13 (ISET), VR1.2 (WIPER)
SCL: J1.4, J2.4, U2.14 (SCL)
SDA: J1.3, J2.3, U2.1 (SDA)

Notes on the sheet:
Connector
